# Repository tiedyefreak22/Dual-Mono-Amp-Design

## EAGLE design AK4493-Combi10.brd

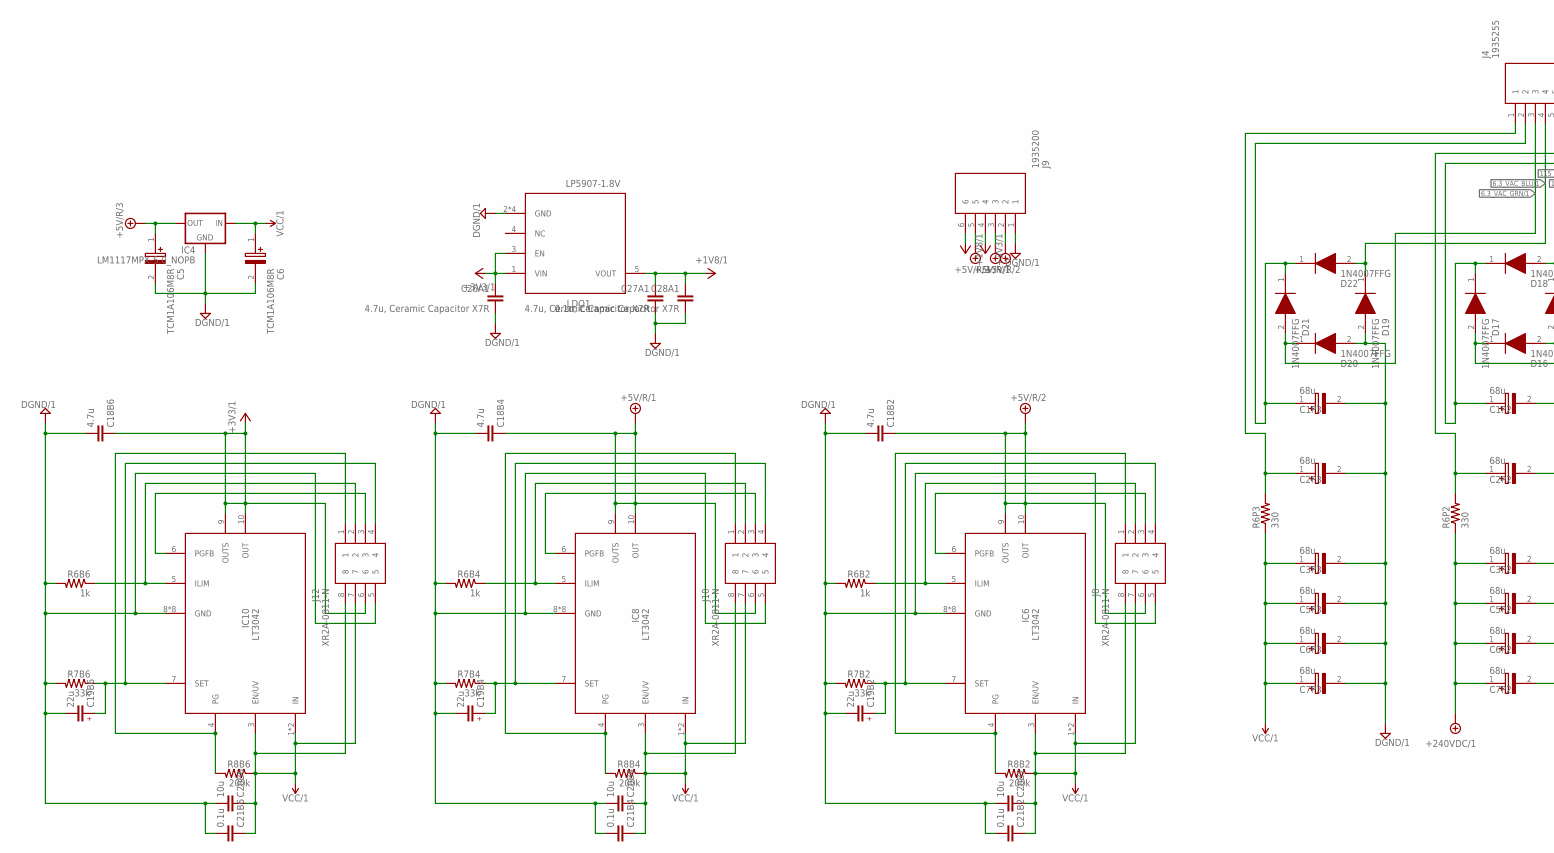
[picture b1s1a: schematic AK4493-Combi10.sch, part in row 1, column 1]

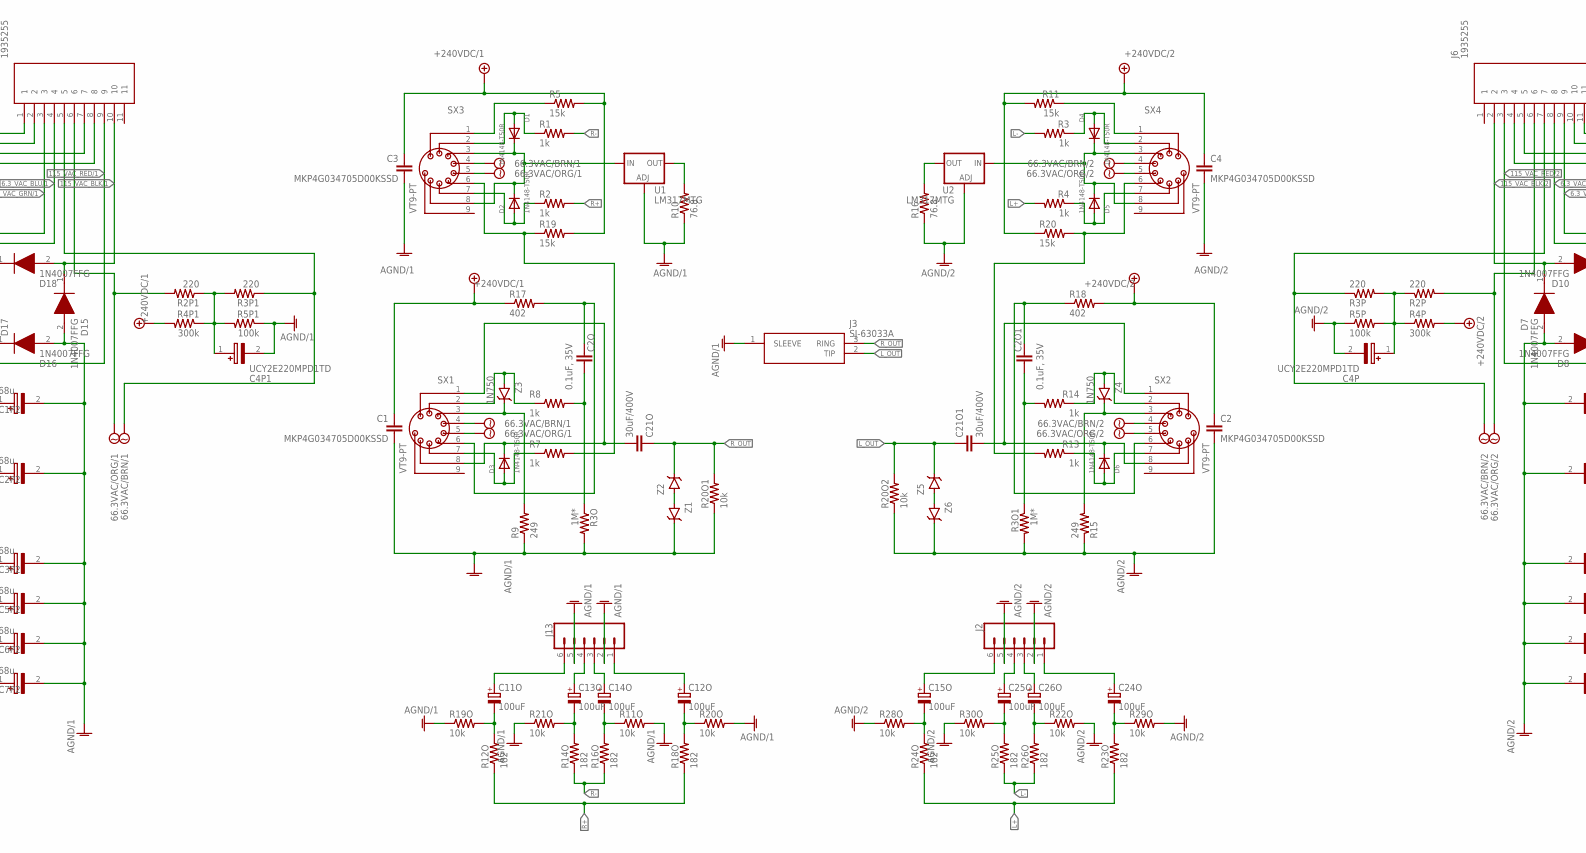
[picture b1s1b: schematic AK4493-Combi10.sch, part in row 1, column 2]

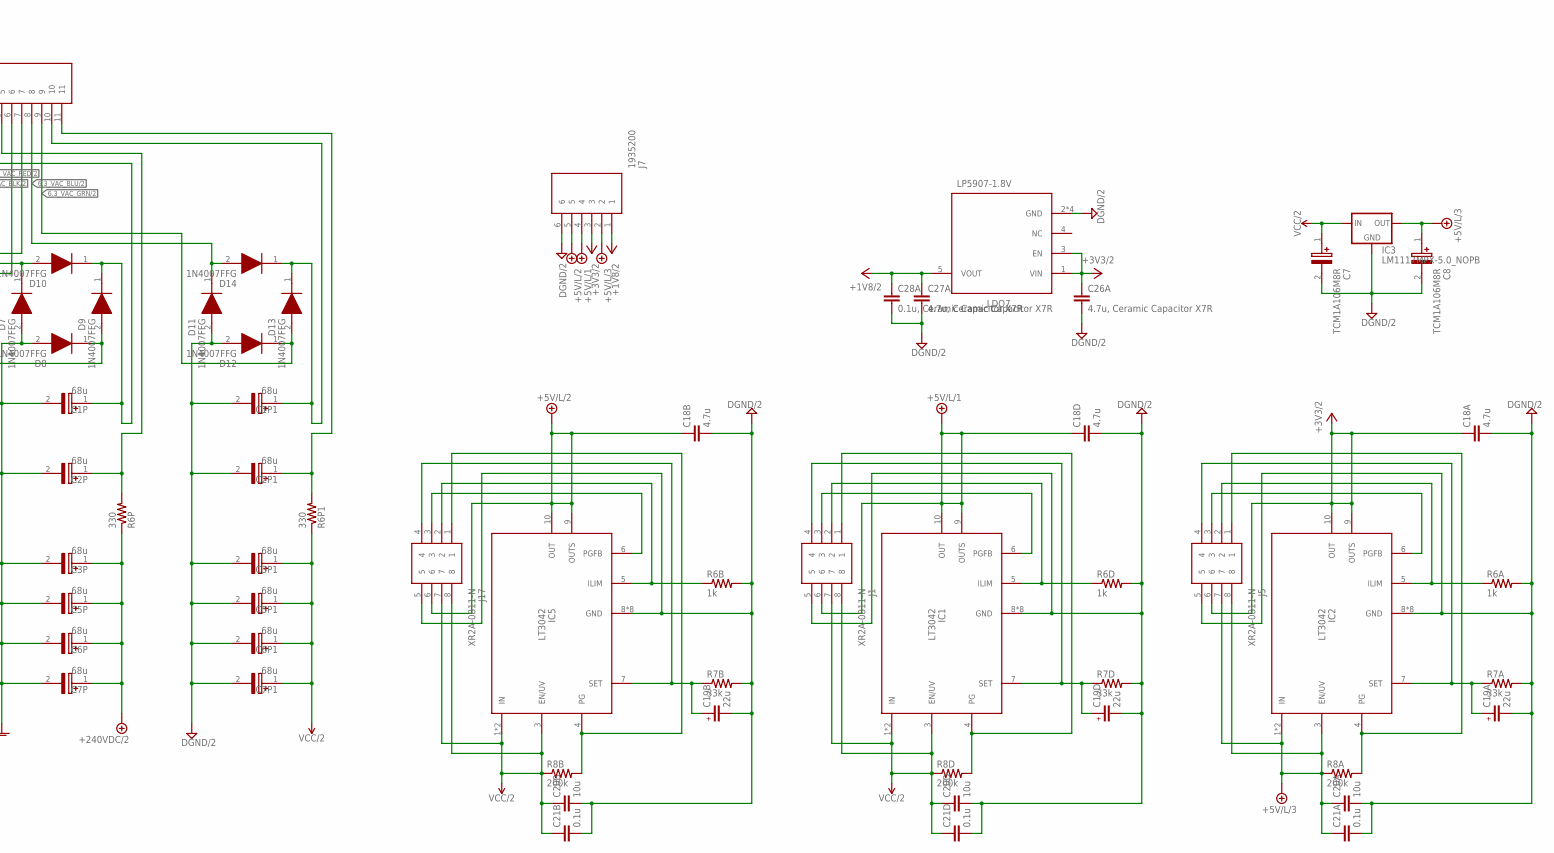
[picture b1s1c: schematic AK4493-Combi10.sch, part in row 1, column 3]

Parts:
C1, C2, C3, C4: MKP4G034705D00KSSD
C1P, C1P1, C1P2, C1P3, C2P, C2P1, C2P2, C2P3, C3P, C3P1, C3P2, C3P3, C5P, C5P1, C5P2, C5P3, C6P, C6P1, C6P2, C6P3, C7P, C7P1, C7P2, C7P3: 68u; CAPPRD750W80D1475H4700
C2O, C2O1: 0.1uF, 35V; MKS4B031002A00JC00
C4P, C4P1: UCY2E220MPD1TD; CAPPRD500W60D1025H1750
C5, C6, C7, C8: TCM1A106M8R; CAPPM168X90N
C11O, C12O, C13O, C14O, C15O, C24O, C25O, C26O: 100uF; CAPPRD350W60D825H1300
C18A, C18B, C18B2, C18B4, C18B6, C18D: 4.7u; CAPC2013X140N
C19A, C19B, C19B2, C19B4, C19B6, C19D: 22u; C1206
C20A, C20B, C20B2, C20B4, C20B6, C20D: 10u; CAPC2012X135N
C21A, C21B, C21B2, C21B4, C21B6, C21D: 0.1u; CAPC2012X135N
C21O, C21O1: 30uF/400V; DCP4G056007GD4KSSD
C26A, C26A1, C27A, C27A1: 4.7u, Ceramic Capacitor X7R; CAPC2013X140N
C28A, C28A1: 0.1u, Ceramic Capacitor X7R; CAPC2012X135N
D1, D2, D3, D4, D5, D6: 1N4148-T50R; DIOAD1068W53L380D172
D7, D8, D9, D10, D11, D12, D13, D14, D15, D16, D17, D18, D19, D20, D21, D22: 1N4007FFG; DIOAD1405W86L465D235
IC1, IC2, IC5, IC6, IC8, IC10: LT3042; SOP50P490X110-11N
IC3, IC4: LM1117MPX-5.0_NOPB; SOT230P700X180-4N
J1, J5, J8, J10, J12, J17: XR2A-0811-N; DIPS762W51P254L1016H390Q8N
J2, J13: CONN_06SILK_FEMALE_PTH; 1X06
J3: SJ-63033A; SJ63033A
J4, J6: 1935255
J7, J9: 1935200
LDO1, LDO7: LP5907-1.8V; SOT95P280X145-5N
R1, R2, R3, R4, R7, R8, R13, R14: 1k; 0207/10
R2P, R2P1, R3P, R3P1: 220; 0411/15
R3O, R3O1: 1M*; 0207/10
R4P, R4P1: 300k; 0411/15
R5, R11, R19, R20: 15k; 0411/15
R5P, R5P1: 100k; 0411/15
R6A, R6B, R6B2, R6B4, R6B6, R6D: 1k; RESC2012X60N
R6P, R6P1, R6P2, R6P3: 330; 0411/15
R7A, R7B6: 33k; RESC2012X65N
R7B, R7B2, R7B4, R7D: 33k; R0805
R8A, R8B, R8B2, R8B4, R8B6, R8D: 200k; R0805
R9, R15: 249; 0207/10
R10, R16: 76.8; 0207/10
R11O, R19O, R20O, R20O1, R20O2, R21O, R22O, R28O, R29O, R30O: 10k; 0207/10
R12O, R14O, R16O, R18O, R23O, R24O, R25O, R26O: 182; 0207/10
R17, R18: 402; 0617/22
SX1, SX2, SX3, SX4: VT9-PT
U1, U2: LM317MTG; TO254P482X997X2018-3P
Z1, Z2, Z5, Z6: BZX79-C16,113; DIOAD1165W56L425D185
Z3, Z4: 1N750; DIOAD1256W56L444D203

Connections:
6.3_VAC_BLU/1: D19.1 (K), D22.2 (A), J4.4
6.3_VAC_BLU/2: D11.1 (K), D14.2 (A), J6.8
6.3_VAC_GRN/1: D20.1 (K), D21.2 (A), J4.3
6.3_VAC_GRN/2: D12.1 (K), D13.2 (A), J6.9
66.3VAC/BRN/1: J4.5, R3P1.1, SX1.4, SX3.4
66.3VAC/BRN/2: J6.7, R3P.1, SX2.4, SX4.4
66.3VAC/ORG/1: J4.6, R2P1.2, SX1.5, SX3.5
66.3VAC/ORG/2: J6.6, R2P.2, SX2.5, SX4.5
115_VAC_BLK/1: D15.1 (K), D18.2 (A), J4.10
115_VAC_BLK/2: D7.1 (K), D10.2 (A), J6.2
115_VAC_RED/1: D16.1 (K), D17.2 (A), J4.9
115_VAC_RED/2: D8.1 (K), D9.2 (A), J6.3
+1V8/1: C27A1.1, C28A1.1, J9.6, LDO1.5 (VOUT)
+1V8/2: C27A.1, C28A.1, J7.1, LDO7.5 (VOUT)
+3V3/1: C18B6.1, C26A1.1, IC10.9 (OUTS), IC10.10 (OUT), J9.4, J12.6, LDO1.1 (VIN), LDO1.3 (EN)
+3V3/2: C18A.1, C26A.1, IC2.9 (OUTS), IC2.10 (OUT), J5.6, J7.3, LDO7.1 (VIN), LDO7.3 (EN)
+5V/L/1: C18D.1, IC1.9 (OUTS), IC1.10 (OUT), J1.6, J7.4
+5V/L/2: C18B.1, IC5.9 (OUTS), IC5.10 (OUT), J7.5, J17.6
+5V/L/3: C8.1 (+), C20A.1, C21A.1, IC2.1 (IN), IC2.2 (IN), IC2.3 (EN/UV), IC3.2 (OUT), IC3.4 (OUT), J5.7, J5.8, J7.2, R8A.1
+5V/R/1: C18B4.1, IC8.9 (OUTS), IC8.10 (OUT), J9.3, J10.6
+5V/R/2: C18B2.1, IC6.9 (OUTS), IC6.10 (OUT), J8.6, J9.2
+5V/R/3: C5.1 (+), IC4.2 (OUT), IC4.4 (OUT), J9.5
+240VDC/1: C1.1, C3.1, C3P2.1 (+), C5P2.1 (+), C6P2.1 (+), C7P2.1 (+), R4P1.2, R5.2, R6P2.1, R17.1, R19.2
+240VDC/2: C2.1, C3P.1 (+), C4.1, C5P.1 (+), C6P.1 (+), C7P.1 (+), R4P.2, R6P.1, R11.2, R18.2, R20.1
AGND/1: C1.2, C1P2.2 (-), C2P2.2 (-), C3.2, C3P2.2 (-), C4P1.2 (-), C5P2.2 (-), C6P2.2 (-), C7P2.2 (-), D15.2 (A), D16.2 (A), J3.1 (SLEEVE), J13.2, J13.5, R3O.2, R5P1.1, R9.1, R10.1, R11O.2, R19O.1, R20O.2, R20O1.1, R21O.1, U1.1 (ADJ), Z1.1 (C)
AGND/2: C1P.2 (-), C2.2, C2P.2 (-), C3P.2 (-), C4.2, C4P.2 (-), C5P.2 (-), C6P.2 (-), C7P.2 (-), D7.2 (A), D8.2 (A), J2.2, J2.5, R3O1.2, R5P.1, R15.1, R16.1, R20O2.1, R22O.2, R28O.1, R29O.2, R30O.1, U2.1 (ADJ), Z6.1 (C)
DGND/1: C1P3.2 (-), C2P3.2 (-), C3P3.2 (-), C5.2 (-), C5P3.2 (-), C6.2 (-), C6P3.2 (-), C7P3.2 (-), C18B2.2, C18B4.2, C18B6.2, C19B2.2, C19B2.DGND (2), C19B4.2, C19B4.DGND (2), C19B6.2, C19B6.DGND (2), C20B2.2, C20B4.2, C20B6.2, C21B2.2, C21B4.2, C21B6.2, C26A1.2, C27A1.2, C28A1.2, D19.2 (A), D20.2 (A), IC4.1 (GND), IC6.8 (GND), IC6.11 (GND), IC6.P$1 (GND), IC6.P$2 (GND), IC6.P$3 (GND), IC6.P$4 (GND), IC6.P$5 (GND), IC6.P$6 (GND), IC8.8 (GND), IC8.11 (GND), IC8.P$1 (GND), IC8.P$2 (GND), IC8.P$3 (GND), IC8.P$4 (GND), IC8.P$5 (GND), IC8.P$6 (GND), IC10.8 (GND), IC10.11 (GND), IC10.P$1 (GND), IC10.P$2 (GND), IC10.P$3 (GND), IC10.P$4 (GND), IC10.P$5 (GND), IC10.P$6 (GND), J8.5, J9.1, J10.5, J12.5, LDO1.2 (GND), LDO1.DGND (GND), LDO1.DGND2 (GND), LDO1.DGND3 (GND), R6B2.2, R6B4.2, R6B6.2, R7B2.2, R7B4.2, R7B6.2
DGND/2: C1P1.2 (-), C2P1.2 (-), C3P1.2 (-), C5P1.2 (-), C6P1.2 (-), C7.2 (-), C7P1.2 (-), C8.2 (-), C18A.2, C18B.2, C18D.2, C19A.2, C19A.DGND (2), C19B.2, C19B.DGND (2), C19D.2, C19D.DGND (2), C20A.2, C20B.2, C20D.2, C21A.2, C21B.2, C21D.2, C26A.2, C27A.2, C28A.2, D11.2 (A), D12.2 (A), IC1.8 (GND), IC1.11 (GND), IC1.P$1 (GND), IC1.P$2 (GND), IC1.P$3 (GND), IC1.P$4 (GND), IC1.P$5 (GND), IC1.P$6 (GND), IC2.8 (GND), IC2.11 (GND), IC2.P$1 (GND), IC2.P$2 (GND), IC2.P$3 (GND), IC2.P$4 (GND), IC2.P$5 (GND), IC2.P$6 (GND), IC3.1 (GND), IC5.8 (GND), IC5.11 (GND), IC5.P$1 (GND), IC5.P$2 (GND), IC5.P$3 (GND), IC5.P$4 (GND), IC5.P$5 (GND), IC5.P$6 (GND), J1.5, J5.5, J7.6, J17.5, LDO7.2 (GND), LDO7.DGND (GND), LDO7.DGND2 (GND), LDO7.DGND3 (GND), R6A.2, R6B.2, R6D.2, R7A.2, R7B.2, R7D.2
L+: R4.2, R23O.1, R24O.1
L-: R3.2, R25O.1, R26O.1
L_OUT: C21O1.1, C21O1.4 (1), J3.2 (TIP), R20O2.2, Z5.1 (C)
unnamed: R7.2, R19.1, SX3.6
unnamed: R8.1, SX1.2, Z3.2 (A)
unnamed: C21O1.2, C21O1.3 (2), D6.1 (C), SX2.1, SX2.8
unnamed: D4.2 (A), R3.1, SX4.2
unnamed: D5.2 (A), R4.1, SX4.7
unnamed: D1.2 (A), R1.1, SX3.2
unnamed: D4.1 (C), D5.1 (C), SX4.3, SX4.8, U2.3 (IN)
unnamed: R11.1, SX4.1
unnamed: R13.2, R20.2, SX4.6
unnamed: C11O.1 (+), J13.6
unnamed: C11O.2 (-), R12O.2, R19O.2
unnamed: C15O.1 (+), J2.6
unnamed: D2.2 (A), R2.1, SX3.7
unnamed: R14.1, SX2.2, Z4.2 (A)
unnamed: C12O.1 (+), J13.1
unnamed: C2O.2, R3O.1, R8.2
unnamed: C2O1.2, R3O1.1, R14.2
unnamed: C21O.2, C21O.3 (2), D3.1 (C), SX1.1, SX1.8
unnamed: C12O.2 (-), R18O.2, R20O.1
unnamed: C15O.2 (-), R24O.2, R28O.2
unnamed: C13O.1 (+), J13.4
unnamed: D1.1 (C), D2.1 (C), SX3.3, SX3.8, U1.3 (IN)
unnamed: D3.2 (A), R7.1, SX1.7
unnamed: C14O.1 (+), J13.3
unnamed: C14O.2 (-), R11O.1, R16O.2
unnamed: R9.2, SX1.3, Z3.1 (C)
unnamed: R15.2, SX2.3, Z4.1 (C)
unnamed: C13O.2 (-), R14O.2, R21O.2
unnamed: D6.2 (A), R13.1, SX2.7
unnamed: C24O.1 (+), J2.1
unnamed: C24O.2 (-), R23O.2, R29O.1
unnamed: C25O.1 (+), J2.4
unnamed: C26O.1 (+), J2.3
unnamed: C26O.2 (-), R22O.1, R26O.2
unnamed: R5.1, SX3.1
unnamed: C25O.2 (-), R25O.2, R30O.2
unnamed: R10.2, U1.2 (OUT)
unnamed: R16.2, U2.2 (OUT)
unnamed: C2O.1, R17.2, SX1.6
unnamed: C2O1.1, R18.1, SX2.6
unnamed: Z1.2 (A), Z2.2 (A)
unnamed: Z5.2 (A), Z6.2 (A)
unnamed: C1P.1 (+), D9.1 (K), D10.1 (K), J6.4
unnamed: C2P.1 (+), J6.5, R6P.2
unnamed: C4P.1 (+), R2P.1, R3P.2, R4P.1, R5P.2
unnamed: IC5.4 (PG), J17.1, R8B.2
unnamed: IC5.5 (ILIM), J17.2, R6B.1
unnamed: IC5.6 (PGFB), J17.3
unnamed: IC1.4 (PG), J1.1, R8D.2
unnamed: IC1.5 (ILIM), J1.2, R6D.1
unnamed: IC1.6 (PGFB), J1.3
unnamed: C19D.1, IC1.7 (SET), J1.4, R7D.1
unnamed: IC2.4 (PG), J5.1, R8A.2
unnamed: IC2.5 (ILIM), J5.2, R6A.1
unnamed: IC2.6 (PGFB), J5.3
unnamed: C19A.1, IC2.7 (SET), J5.4, R7A.1
unnamed: C1P1.1 (+), D13.1 (K), D14.1 (K), J6.10
unnamed: C2P1.1 (+), J6.11, R6P1.2
unnamed: C1P2.1 (+), D17.1 (K), D18.1 (K), J4.8
unnamed: C2P2.1 (+), J4.7, R6P2.2
unnamed: C4P1.1 (+), R2P1.1, R3P1.2, R4P1.1, R5P1.2
unnamed: C1P3.1 (+), D21.1 (K), D22.1 (K), J4.2
unnamed: IC6.4 (PG), J8.1, R8B2.2
unnamed: C19B2.1, IC6.7 (SET), J8.4, R7B2.1
unnamed: IC6.5 (ILIM), J8.2, R6B2.1
unnamed: IC6.6 (PGFB), J8.3
unnamed: C2P3.1 (+), J4.1, R6P3.2
unnamed: IC8.4 (PG), J10.1, R8B4.2
unnamed: C19B4.1, IC8.7 (SET), J10.4, R7B4.1
unnamed: IC8.5 (ILIM), J10.2, R6B4.1
unnamed: IC8.6 (PGFB), J10.3
unnamed: IC10.4 (PG), J12.1, R8B6.2
unnamed: C19B6.1, IC10.7 (SET), J12.4, R7B6.1
unnamed: IC10.5 (ILIM), J12.2, R6B6.1
unnamed: IC10.6 (PGFB), J12.3
unnamed: C19B.1, IC5.7 (SET), J17.4, R7B.1
R+: R2.2, R12O.1, R18O.1
R-: R1.2, R14O.1, R16O.1
R_OUT: C21O.1, C21O.4 (1), J3.3 (RING), R20O1.2, Z2.1 (C)
VCC/1: C3P3.1 (+), C5P3.1 (+), C6.1 (+), C6P3.1 (+), C7P3.1 (+), C20B2.1, C20B4.1, C20B6.1, C21B2.1, C21B4.1, C21B6.1, IC4.3 (IN), IC6.1 (IN), IC6.2 (IN), IC6.3 (EN/UV), IC8.1 (IN), IC8.2 (IN), IC8.3 (EN/UV), IC10.1 (IN), IC10.2 (IN), IC10.3 (EN/UV), J8.7, J8.8, J10.7, J10.8, J12.7, J12.8, R6P3.1, R8B2.1, R8B4.1, R8B6.1
VCC/2: C3P1.1 (+), C5P1.1 (+), C6P1.1 (+), C7.1 (+), C7P1.1 (+), C20B.1, C20D.1, C21B.1, C21D.1, IC1.1 (IN), IC1.2 (IN), IC1.3 (EN/UV), IC3.3 (IN), IC5.1 (IN), IC5.2 (IN), IC5.3 (EN/UV), J1.7, J1.8, J17.7, J17.8, R6P1.1, R8B.1, R8D.1

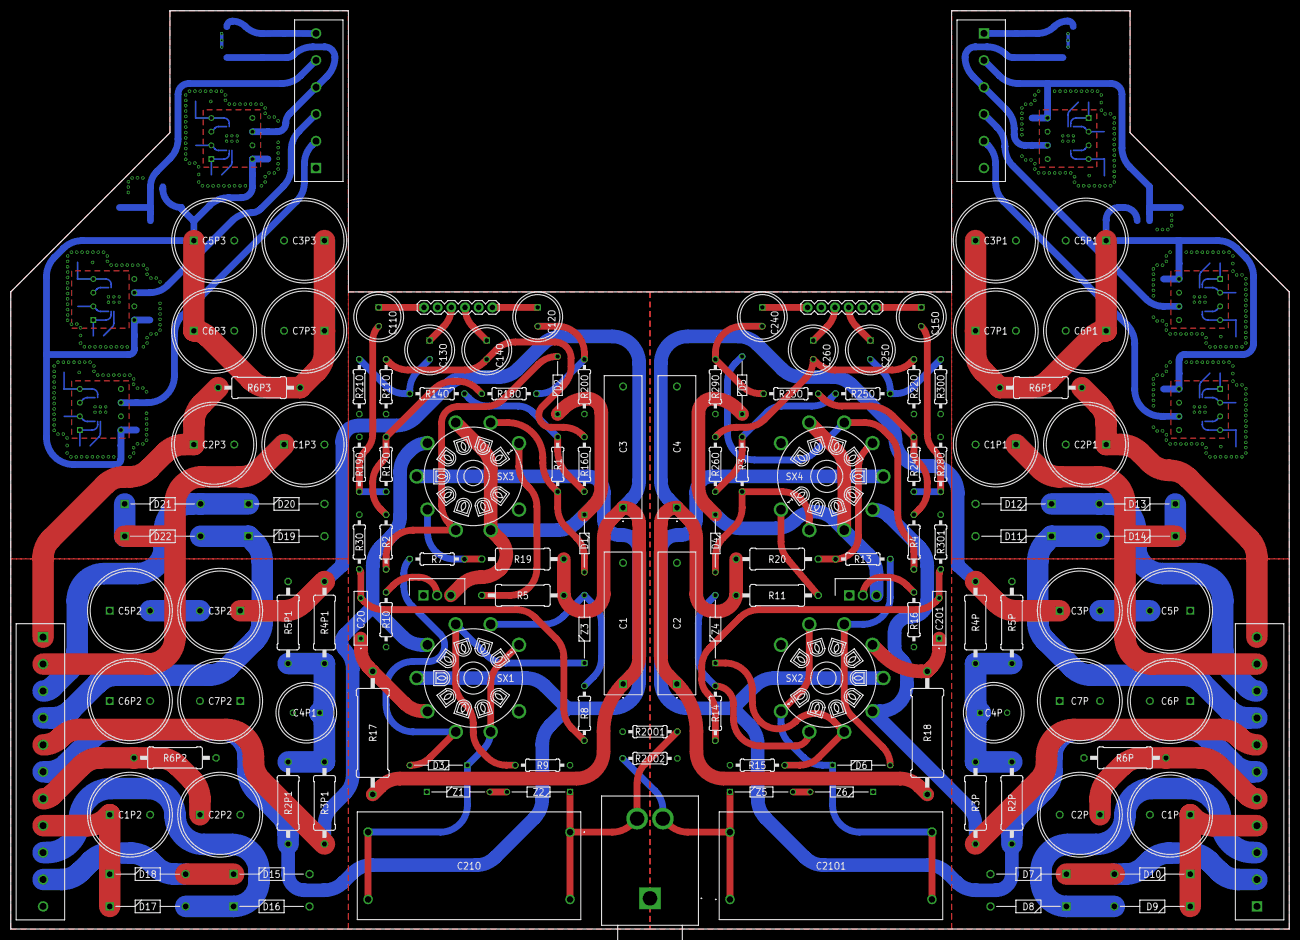
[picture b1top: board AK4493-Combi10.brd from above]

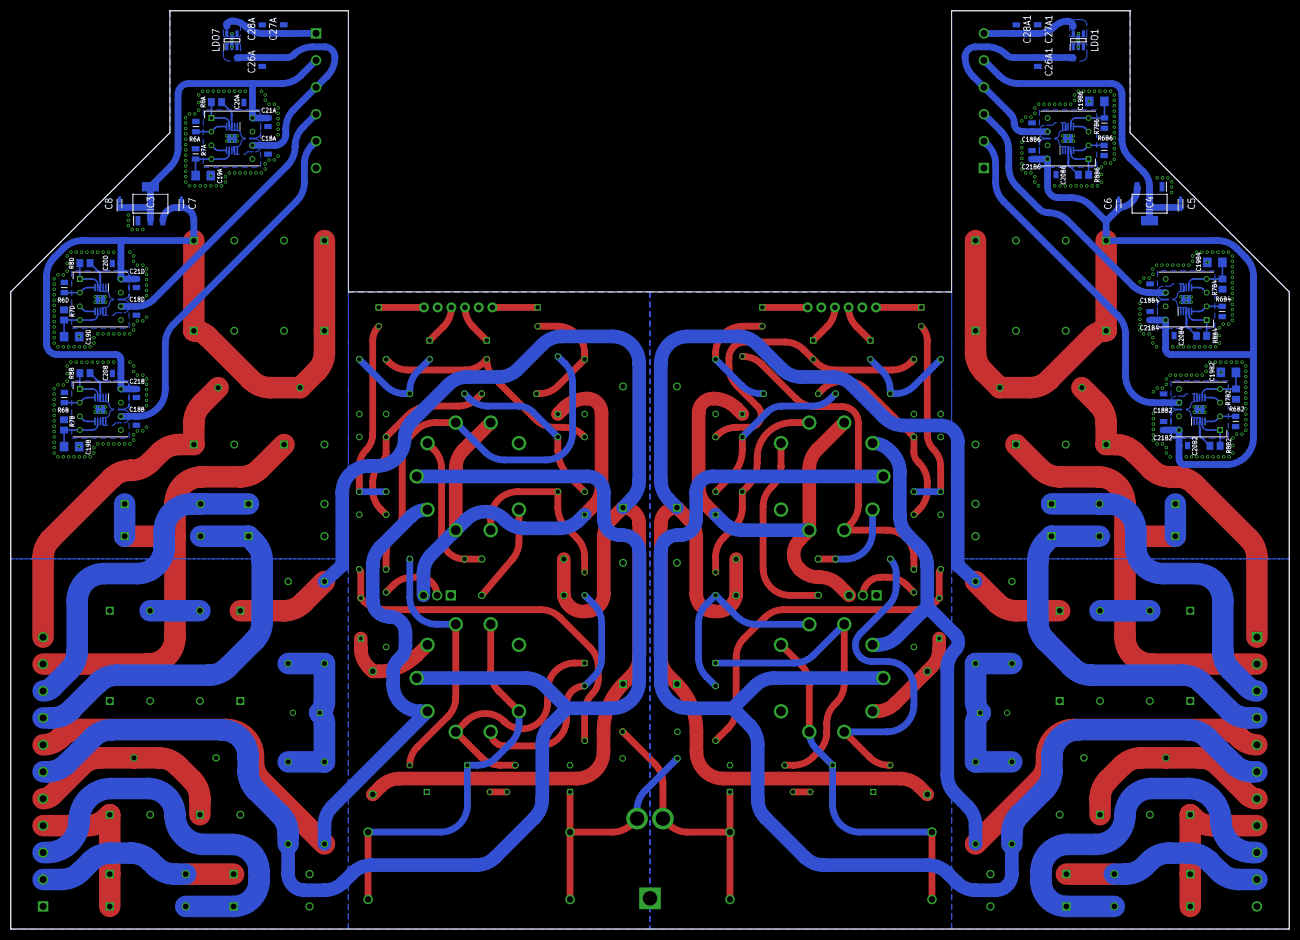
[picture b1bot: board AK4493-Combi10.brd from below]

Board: 2 copper layers, 237.4 x 170.5 mm, 201 parts (68 on the bottom side), 112 nets.

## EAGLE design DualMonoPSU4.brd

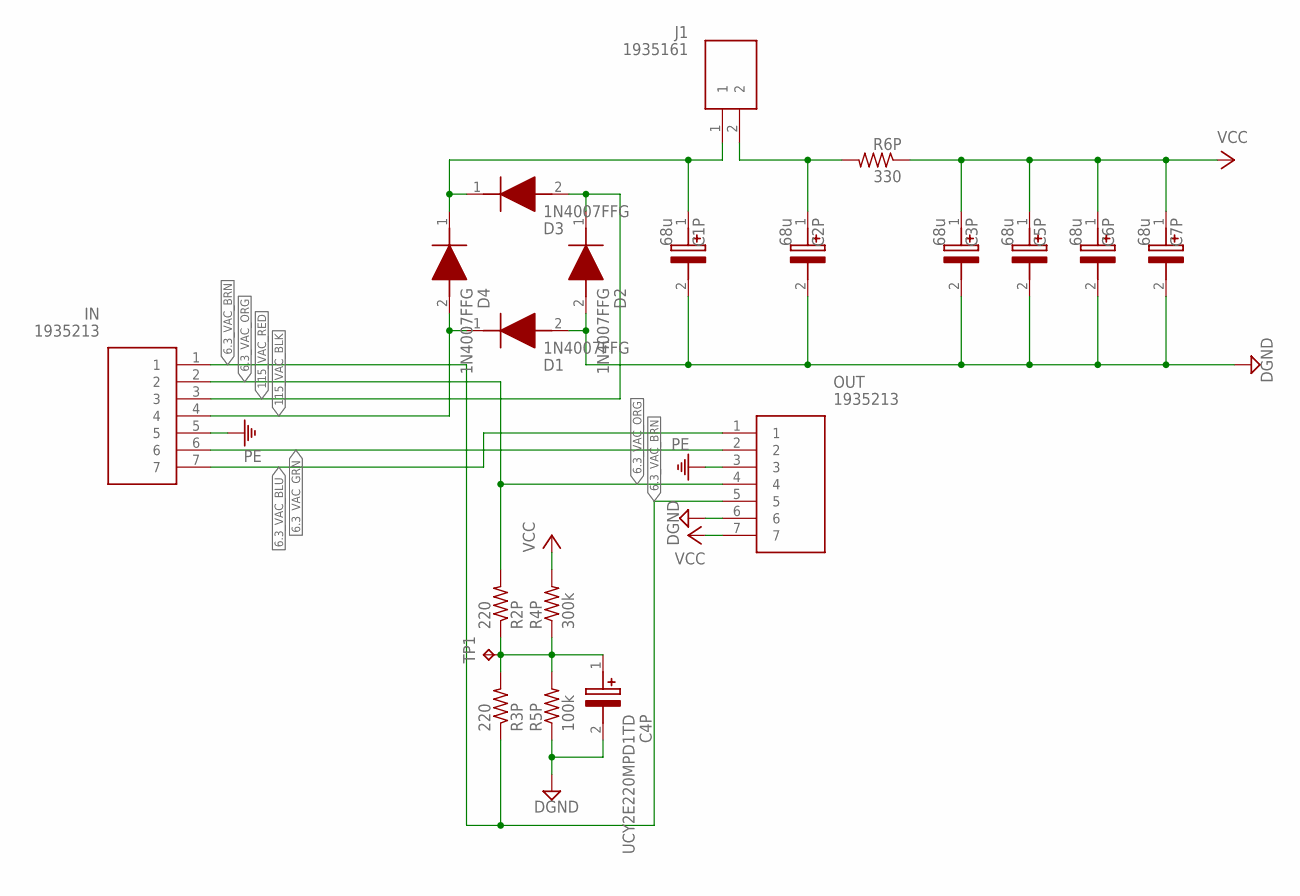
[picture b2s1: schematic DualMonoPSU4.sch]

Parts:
C1P, C2P, C3P, C5P, C6P, C7P: 68u; CAPPRD750W80D1475H4700
C4P: UCY2E220MPD1TD; CAPPRD500W60D1025H1750
D1, D2, D3, D4: 1N4007FFG; DIOAD1405W86L465D235
IN: 1935213
J1: 1935161
OUT: 1935213
R2P, R3P: 220; 0411/15
R4P: 300k; 0411/15
R5P: 100k; 0411/15
R6P: 330; 0411/15
TP1: TPB2,54; B2,54

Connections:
6.3_VAC_BLU: IN.7, OUT.1
6.3_VAC_BRN: IN.1, OUT.5, R3P.1
6.3_VAC_GRN: IN.6, OUT.2
6.3_VAC_ORG: IN.2, OUT.4, R2P.2
115_VAC_BLK: D1.1 (K), D4.2 (A), IN.4
115_VAC_RED: D2.1 (K), D3.2 (A), IN.3
DGND: C1P.2 (-), C2P.2 (-), C3P.2 (-), C4P.2 (-), C5P.2 (-), C6P.2 (-), C7P.2 (-), D1.2 (A), D2.2 (A), OUT.6, R5P.1
unnamed: C1P.1 (+), D3.1 (K), D4.1 (K), J1.1
unnamed: C2P.1 (+), J1.2, R6P.2
unnamed: C4P.1 (+), R2P.1, R3P.2, R4P.1, R5P.2, TP1.TP
PE: IN.5, OUT.3
VCC: C3P.1 (+), C5P.1 (+), C6P.1 (+), C7P.1 (+), OUT.7, R4P.2, R6P.1

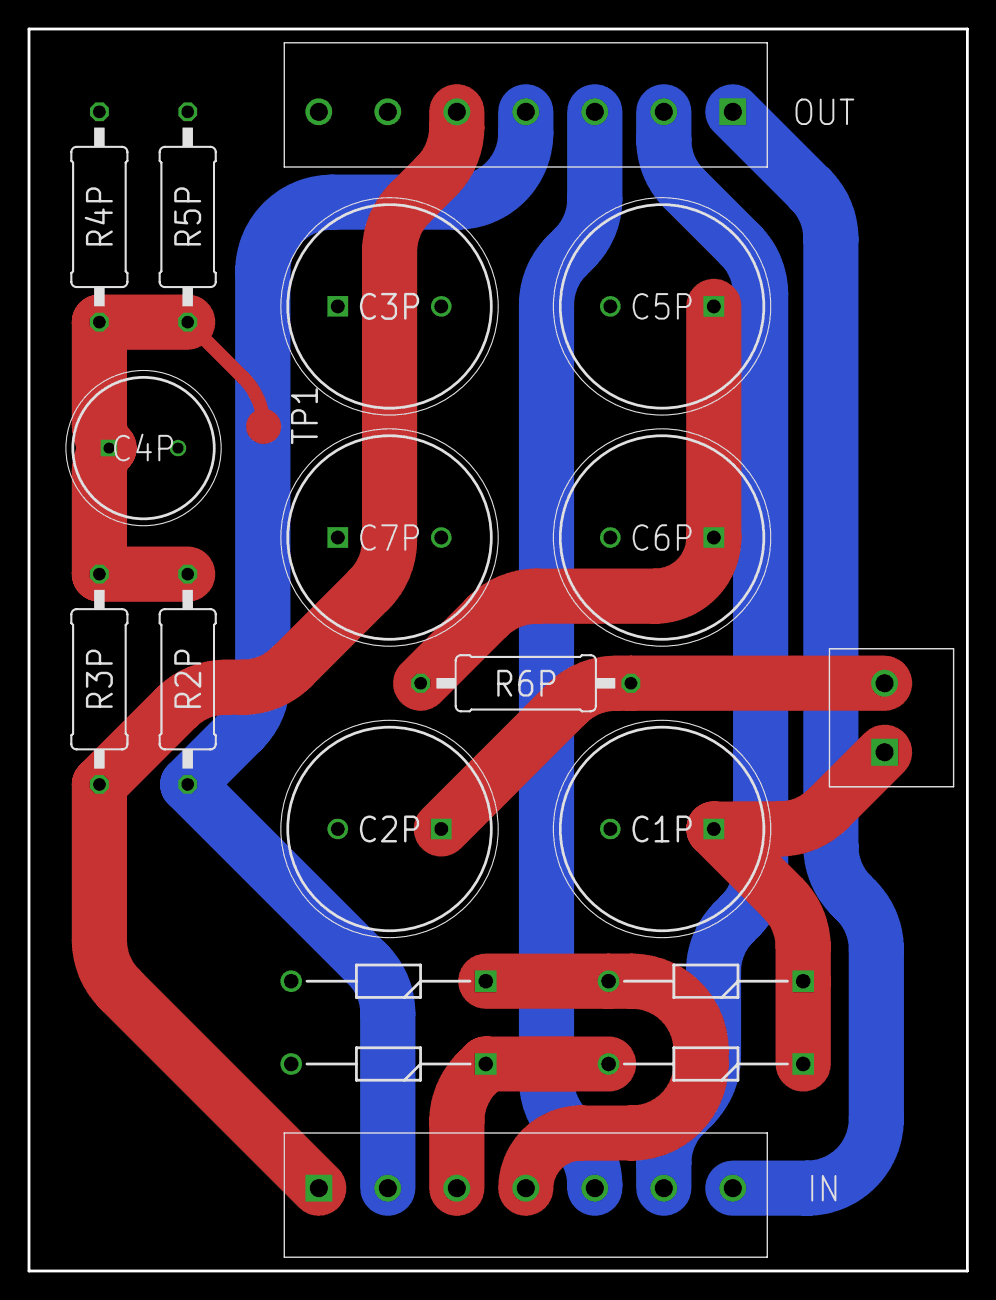
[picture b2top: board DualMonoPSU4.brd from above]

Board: 2 copper layers, 68.0 x 90.0 mm, 20 parts (0 on the bottom side), 12 nets.

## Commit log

2024-04-01 More work and part tracking
2024-09-28 Added gitignore
2024-12-03 Adding Fusion DAC Output Stage archive
2024-12-20 Added AK4493 breakout boards
2025-01-03 submitted PSU board for fabrication
2025-01-05 Organization and Master BOM
2025-01-13 Updated AK9943 board with improvements and worked master BOM
2025-01-18 Created RGB Volume Control script
2025-01-19 Can read encoder, switch, and change led
2025-01-19 added mute turning red and beginning of volume led changes
2025-01-20 Adding dimdim software and teensy pinout diagram
2025-01-21 Improvements and implemented rotational led changes. Need to fix intermittent mute red led
2025-01-21 Adding AK4493 control files and finished led color control
2025-01-24 Fixed length of traces
2025-01-29 Adding LT3042 breakout
2025-01-29 Added SN74ABT273DBR breakout
2025-01-29 Added curve to led volume control
2025-02-08 Updating board for breakout boards
2025-02-14 Progress
2025-02-18 Update Output stage with fusion export
2025-02-23 Getting closer
2025-02-23 Finished design and generated gerbers
2025-03-01 Combi progress
2025-03-11 Maybe done?
2025-03-12 More slight changes
2025-04-06 Adding triode plate curves calc file
2025-04-06 Adding plate curves pickle file
2025-04-08 Added 3d manifold
2025-04-13 Abandoned Koren model but implemented 3d manifold "lookup"
2025-04-13 progress!
2025-04-14 Big progress
2025-04-19 good progress
2025-04-24 Maybe progress?
2025-04-25 Adding SPICE Models
2025-04-25 Adding 12AX7 Spec sheet
2025-04-26 Added new tubes and improvements
2025-04-26 Added white cathode follower SPICE
2025-04-26 Moved gitignore
2025-04-27 Working on LTSpice Model
2025-04-27 Spice Progress
2025-04-27 Ran optimize point with 5687
2025-05-08 Adding more SPICE sims
2025-05-09 Updated SPICE files
2025-05-09 Started new output stage and organization
2025-05-09 Ran tube optimizations
2025-05-09 Finished schematic and working layout
2025-05-11 Fixed schematic
2025-05-17 Finished routing
2025-05-18 Finished part swaps
2025-05-24 added 12AU7 and optimized
2025-07-01 More work with missed resistor
2025-07-02 Finished updated design
2025-07-04 Adding trimmer resistor for CCS
2025-07-05 Ordered boards
2025-08-19 Added updated triode plate curves file
2025-08-23 New working updated classes
2025-08-26 Organization
2025-08-26 Updated Triode_Plate_Curves9
2025-08-27 Added nearest resistor rounding functionality
2025-09-08 Updated PSU and added headphone protection to output stage
2025-09-10 Added parent classes and ECC99
2025-09-13 Preliminary update complete for new tube
2025-09-14 Added new spice model and work on output stage
2025-09-23 Finished new output stage?
2025-09-24 Updated Triode_Pentode_Plate_Curves10
2025-09-24 Changed Load Line function to simply bracket interpolated values rather than root solve
2025-09-24 Updated 10
2025-09-24 Updated white cathode follower class
2025-09-26 Working Simulate class
2025-09-26 Added 11
2025-09-27 Fixed kinda?
2025-09-27 Updating 11
2025-09-28 Finished boards and spice models
2025-09-28 Started mouser api thing
2025-09-29 Moar progress
2025-10-05 Finished back end, now have to do graph
2025-10-05 Updated BOM and finished Mouser API script
2025-10-05 For real finished mouser api thing
2025-10-19 Fixed lingering issues
2025-10-24 Added AK4493 BOM and Updated Mouser API script accordingly
2025-12-05 Fixed cap model
2025-12-05 Moar combi progress
2025-12-14 Redid LT3042 breakout
2026-02-08 Ordered boards and parts
